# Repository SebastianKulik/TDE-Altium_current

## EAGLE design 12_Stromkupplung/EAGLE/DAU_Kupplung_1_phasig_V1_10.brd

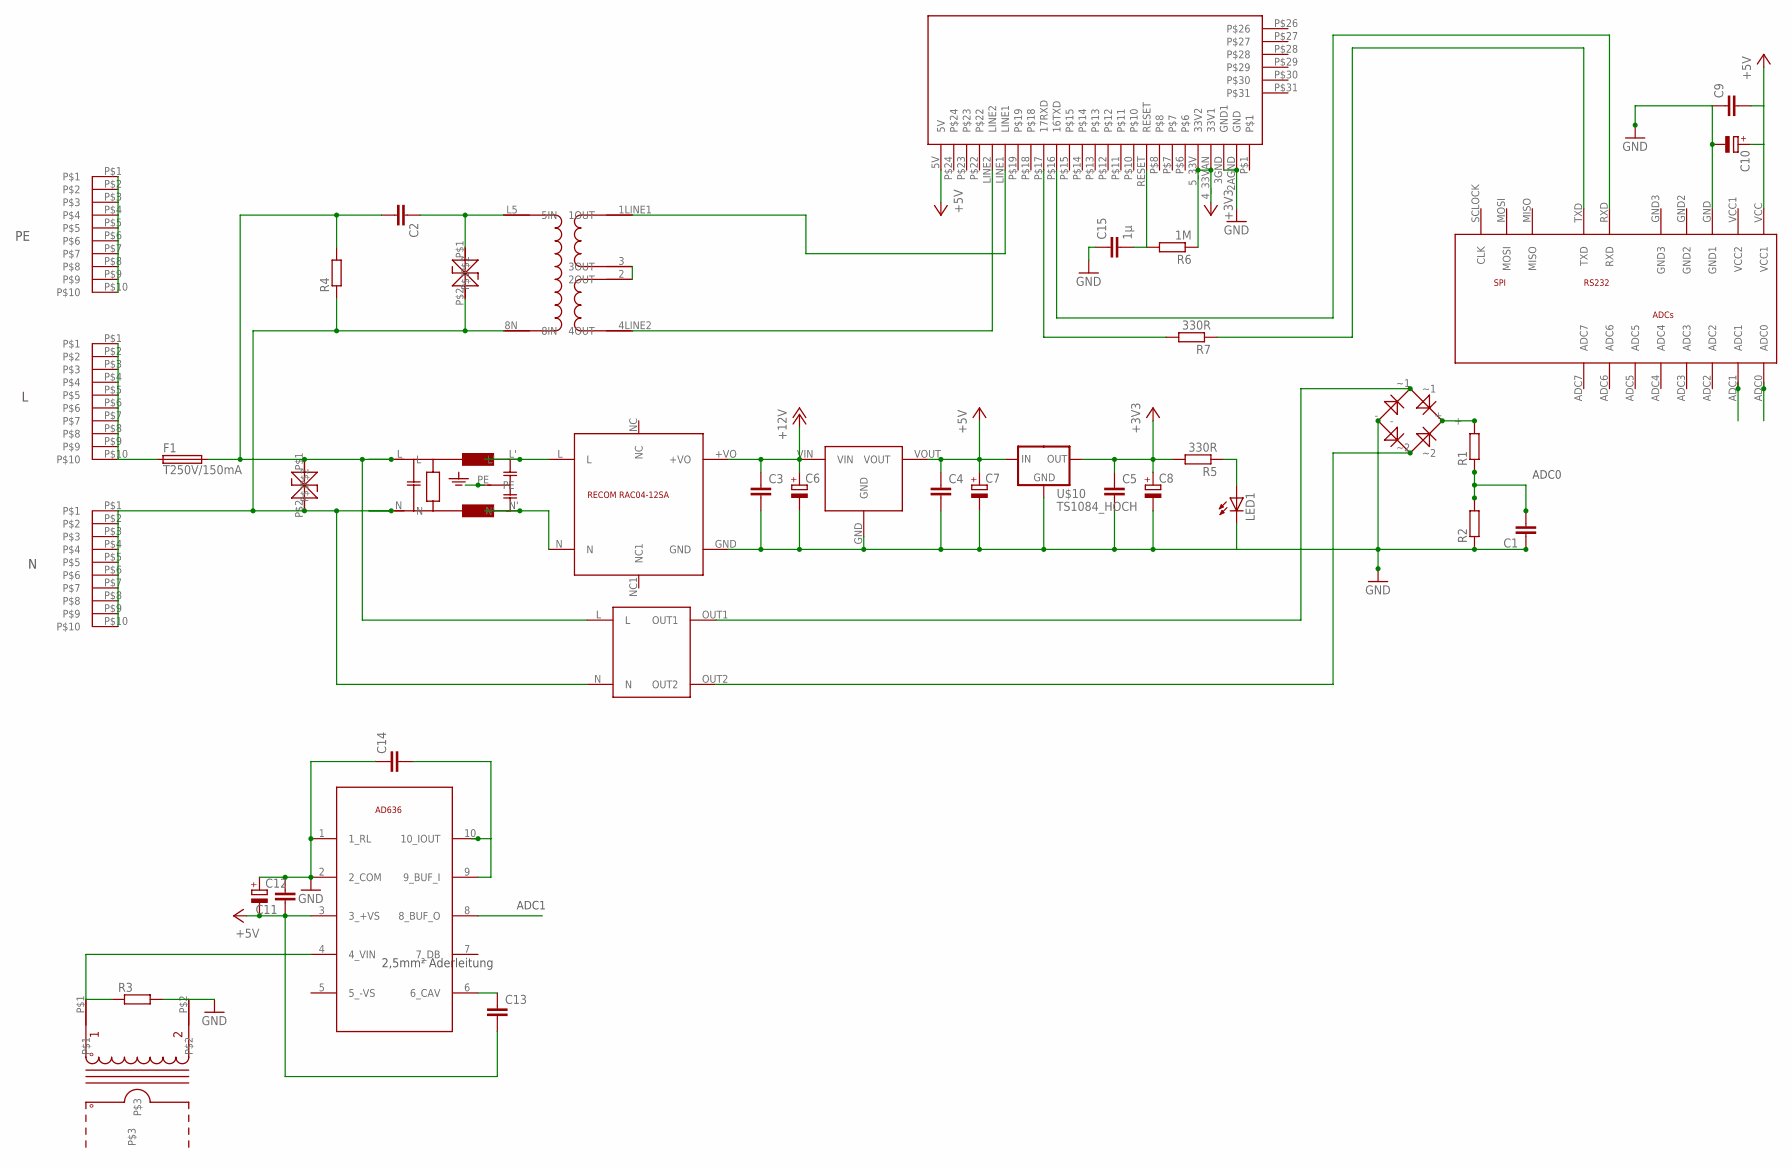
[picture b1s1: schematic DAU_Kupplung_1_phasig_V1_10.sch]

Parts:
C1: C2,5-3; C2.5-3
C2: C-EU225-087X268; C225-087X268
C3, C4, C5, C9, C11, C13, C14: C-EUC0805; C0805
C6, C7, C8: CPOL-EUE2.5-6; E2,5-6
C10, C12: CPOL-EUE2,5-6E; E2,5-6E
C15: 1µ; C0805
F1: T250V/150mA; TR5
L: PRINT_CONNECTOR; FASTON_DOUBLE
LED1: LEDSQR2X5; LED2X5
N: PRINT_CONNECTOR; FASTON_DOUBLE
PE: PRINT_CONNECTOR; FASTON_DOUBLE
R1, R2, R3, R4: R-EU_0204/7; 0204/7
R5, R7: 330R; 0204/7
R6: 1M; 0204/7
U$1: RECOM_RAC04_12SA; RAC04_12SA
U$2: SICHERHEITSTRAFO; TRAFO_0,35VA
U$3: ADUC831_MINIMUM; ADUC_MINIMUM
U$4: IT800
U$5: PLC_UEBERTRAGER_V2; PLC-UEBERTRAGER_V2
U$6: AC1010
U$7: AD636; TO100_10PIN
U$8: RECTIFIER
U$9, U$12: TSV
U$10: TS1084_HOCH
U$11: RECOM_785_05; RECOM785X
U$13: NETZFILTER_05_A; NETZFILTER

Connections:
+3V3: C5.1, C8.+, R5.2, R6.1, U$4.4_33VAN (33V1), U$4.5_33V (33V2), U$10.OUT
+5V: C4.1, C7.+, C9.2, C10.+, C11.1, C12.-, C13.2, U$3.VCC (VCC1), U$4.5V, U$7.3 (3_+VS), U$10.IN, U$11.VOUT
+12V: C3.1, C6.+, U$1.+VO, U$11.VIN
ADC0: C1.2, R1.1, R2.2, U$3.ADC0
ADC1: U$3.ADC1, U$7.8 (8_BUF_O)
GND: C1.1, C3.2, C4.2, C5.2, C6.-, C7.-, C8.-, C9.1, C10.-, C11.2, C12.+, C14.1, C15.1, LED1.K (C), R2.1, R3.2, U$1.GND, U$3.GND (GND1), U$4.2AGND (GND), U$4.3GND (GND1), U$6.P$2, U$7.1 (1_RL), U$7.2 (2_COM), U$8.-, U$10.GND, U$11.GND
unnamed: U$5.2 (2OUT), U$5.3 (3OUT)
unnamed: R7.2, U$4.P$17 (17RXD)
unnamed: U$2.OUT1, U$8.~1
unnamed: U$4.LINE1, U$5.1LINE1 (1OUT)
unnamed: F1.1, L.P$1, L.P$2, L.P$3, L.P$4, L.P$5, L.P$6, L.P$7, L.P$8, L.P$9, L.P$10
unnamed: R1.2, U$8.+
unnamed: R3.1, U$6.P$1, U$7.4 (4_VIN)
unnamed: U$2.OUT2, U$8.~2
unnamed: C2.1, U$5.L5 (5IN), U$12.P$1
unnamed: C2.2, F1.2, R4.2, U$2.L, U$9.P$1, U$13.L
unnamed: U$4.LINE2, U$5.4LINE2 (4OUT)
unnamed: R7.1, U$3.TXD
unnamed: U$3.RXD, U$4.P$16 (16TXD)
unnamed: C14.2, U$7.9 (9_BUF_I), U$7.10 (10_IOUT)
unnamed: C13.1, U$7.6 (6_CAV)
unnamed: N.P$1, N.P$2, N.P$3, N.P$4, N.P$5, N.P$6, N.P$7, N.P$8, N.P$9, N.P$10, R4.1, U$2.N, U$5.8N (8IN), U$9.P$2, U$12.P$2, U$13.N
unnamed: LED1.A, R5.1
unnamed: C15.2, R6.2, U$4.RESET
unnamed: U$1.L, U$13.L'
unnamed: U$1.N, U$13.N'
PE: PE.P$1, PE.P$2, PE.P$3, PE.P$4, PE.P$5, PE.P$6, PE.P$7, PE.P$8, PE.P$9, PE.P$10, U$13.PE

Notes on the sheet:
2,5mm² Aderleitung
ADC0
ADC1

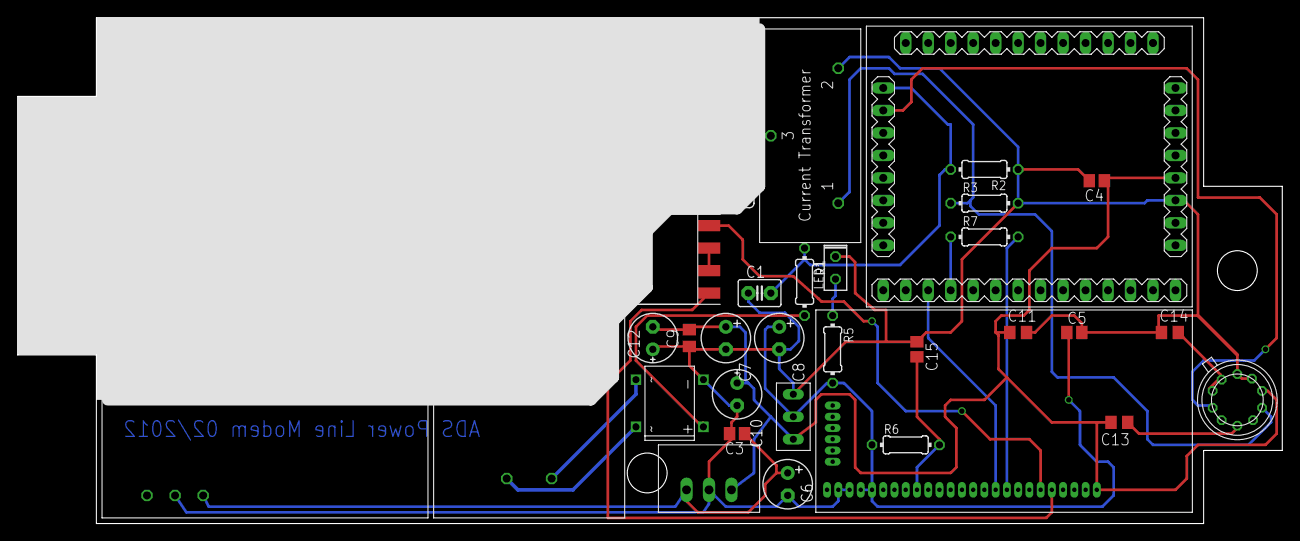
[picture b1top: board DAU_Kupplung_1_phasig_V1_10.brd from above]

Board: 2 copper layers, 142.9 x 57.1 mm, 40 parts (0 on the bottom side), 27 nets.

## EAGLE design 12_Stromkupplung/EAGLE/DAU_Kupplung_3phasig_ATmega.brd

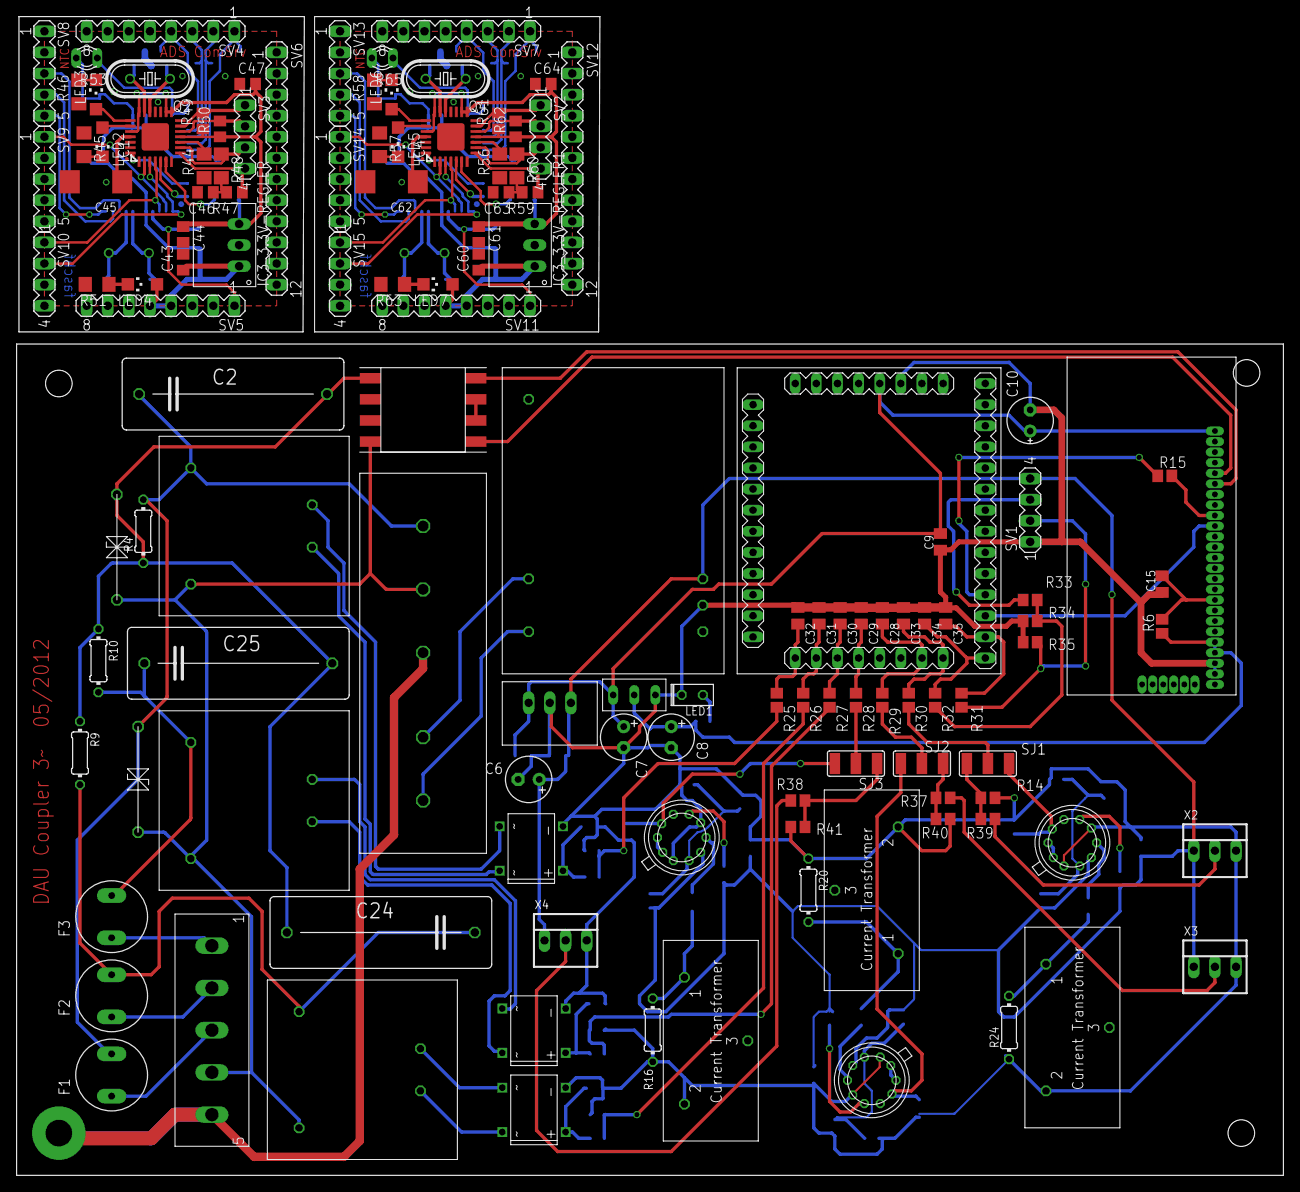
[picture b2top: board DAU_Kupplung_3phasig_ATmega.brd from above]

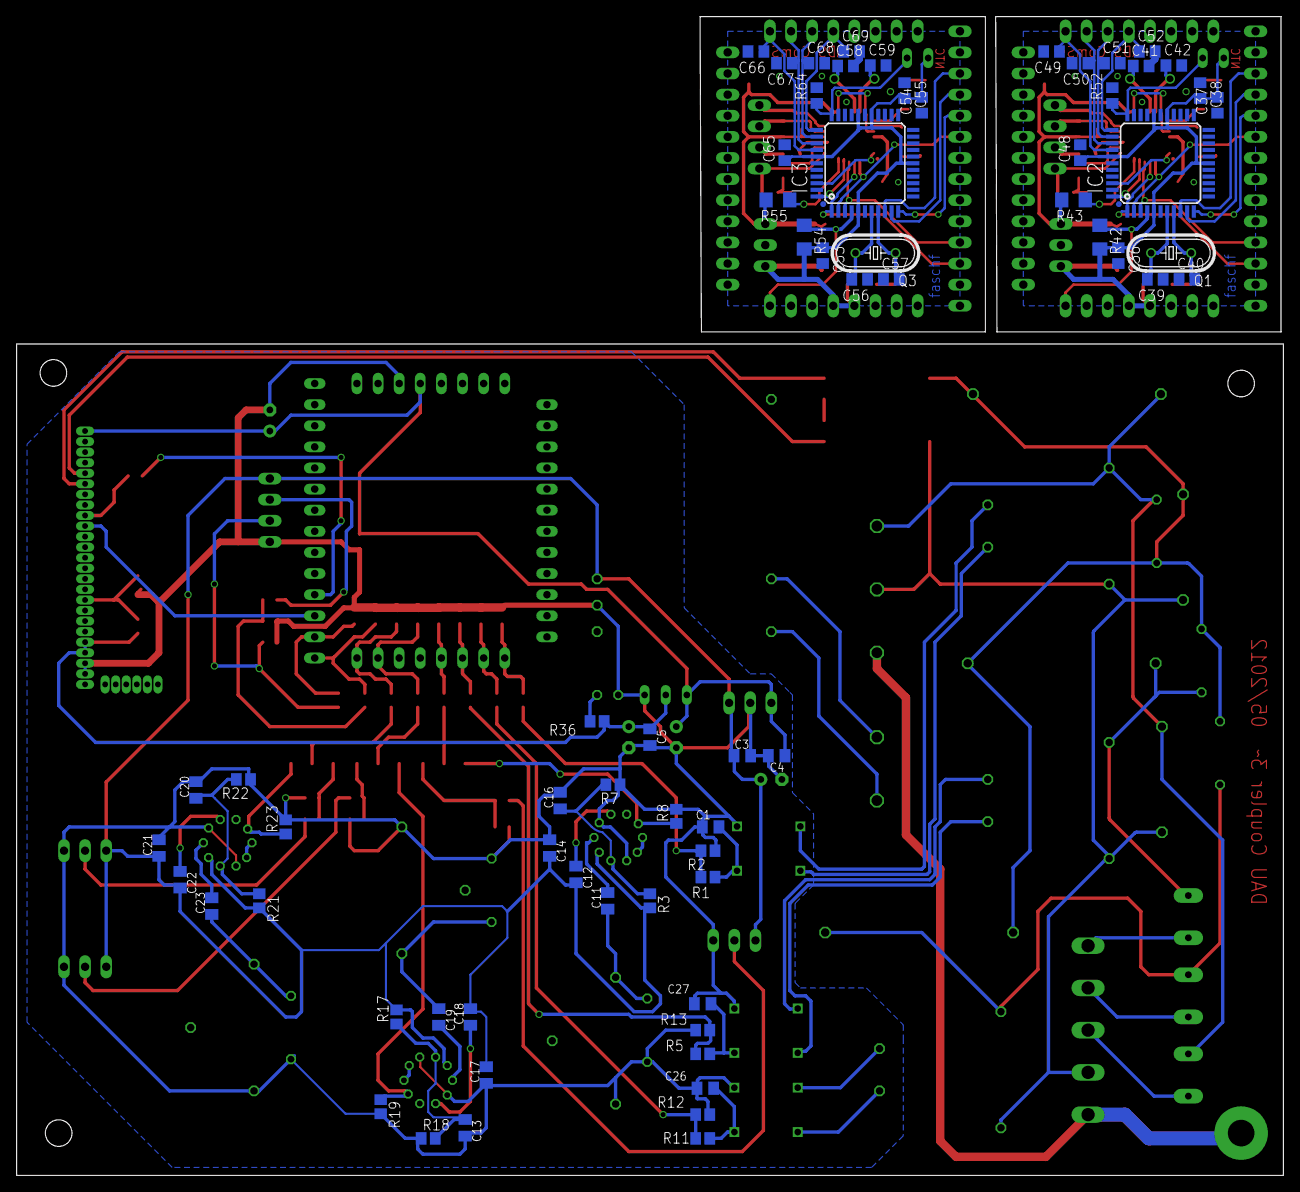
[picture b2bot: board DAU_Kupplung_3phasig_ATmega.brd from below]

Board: 2 copper layers, 152.4 x 139.4 mm, 197 parts (68 on the bottom side), 141 nets.

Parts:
AC1002_1: AC1010
C1, C11, C13, C14, C15, C16, C17, C19, C20, C21, C23, C26, C27: 1µ; C0805K
C2, C24, C25: 470n/270V; C225-087X268
C3, C4, C5, C9, C28, C29, C30, C31, C32, C33, C34, C35: 100n; C0805K
C6, C7, C8: 4,7µ; E2,5-6
C10: 4µ7; E2,5-6E
C12, C18, C22: 4µ7; C0805K
C36, C37, C38, C43, C44, C48, C53, C54, C55, C60, C61, C65: 100n; C0805
C39, C40, C41, C42, C56, C57, C58, C59: 22p; C0805
C45, C62: 10u; SMC_D
C46, C47, C49, C50, C51, C52, C63, C64, C66, C67, C68, C69: 10n; C0805
F1, F2, F3: T250mA/240V; TR5
IC1, IC4: ENC28J60QFN28_LONG_28; QFN28_LONG_ERRLES
IC2, IC3: MEGA32-A; TQFP44
IC3_3.3V-REGLER, IC3_3.3V-REGLER1: 78RECOM; RECOM_3POL
LED1: LED2X5
LED2, LED3, LED4, LED5, LED6, LED7: CHIPLED_1206
P6KE300CA: P6KE300CA; TSV
Q1, Q3: 16MHz; HC49/S
Q2, Q4: 25MHz; HC49/S
R1, R5, R11: 82k; R0805
R2, R12, R13: 33k; R0805
R3, R17, R21: 22k; R0805
R4, R9, R10: 470k; 0204/7
R6: 1M; R0805
R7, R18, R22, R52, R64: 10k; R0805
R8, R19, R23: 4k7; R0805
R14, R40, R41: 220R/33k; R0805
R15, R36: 330R; R0805
R16, R20, R24: 68R; 0204/7
R25, R26, R27, R28, R29, R30, R31, R32: 10R; R0805
R33: 680k; R0805
R34: 470k; R0805
R35: 220R; R0805
R37, R38, R39: 0/82k; R0805
R42, R43, R54, R55: 10k; R1206
R44, R56: 2k2; R1206
R45, R46, R51, R57, R58, R63: 220R; R1206
R47, R49, R50, R59, R61, R62: 51R; R0805
R48, R60: 51R; R1206
R53, R65: P640
SJ1, SJ2, SJ3: SJ_2W
SV1, SV2, SV3, SV10, SV15: MA04-1
SV4, SV5, SV7, SV11: MA08-1
SV6, SV12: MA12-1
SV8, SV9, SV13, SV14: MA05-1
TSV2: TSV
U$1: RECOM_RAC04_12SA; RAC04_12SA
U$2, U$16, U$18: SICHERHEITSTRAFO; TRAFO_0,35VA
U$3: ADUC831_MINIMUM; ADUC_MINIMUM
U$4: MODEMSTECKER; MODEM_FUSS
U$5: PLC_UEBERTRAGER_V2; PLC-UEBERTRAGER_V2
U$7, U$14: AC1010
U$8, U$17, U$19: RECTIFIER
U$10: RECOM_785_05; RECOM785X
U$11: TS1084_HOCH
U$12, U$13, U$15: AD536; TO100_10PIN
U$20: NETZFILTER_05_A; NETZFILTER
X1: CONNECTO_5_POL; CONNECTOR_5_POL
X2, X3, X4: 22-23-2031

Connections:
1_TD+: IC1.13, R49.2, SV3.1
1_TD+1: IC4.13, R61.2, SV2.1
2_TD-: IC1.12, R50.2, SV3.2
2_TD-1: IC4.12, R62.2, SV2.2
3_RD+: IC1.9, R48.1, SV3.3
3_RD+1: IC4.9, R60.1, SV2.3
6_RD-: IC1.8, R47.1, SV3.4
6_RD-1: IC4.8, R59.1, SV2.4
+3V3: C5.1, C8.+, R6.1, R36.1, U$4.P$4, U$4.P$5, U$11.OUT
+5V: C4.1, C7.+, C9.2, C10.+, U$3.VCC, U$4.P$25, U$10.VOUT, U$11.IN
+12V: C3.1, C6.+, C12.2, C14.2, C17.2, C18.2, C21.1, C22.2, R3.2, R17.2, R21.2, SV1.4, U$1.+VO, U$10.VIN, U$12.3, U$13.3, U$15.3, X2.1, X3.1, X4.1
ADC0: C32.1, R25.2, U$3.ADC0
ADC1: C31.1, R26.2, U$3.ADC1
ADC2: C30.1, R27.2, U$3.ADC2
ADC3: C29.1, R28.2, U$3.ADC3
ADC4: C28.1, R29.2, U$3.ADC4
ADC5: C33.1, R30.2, U$3.ADC5
ADC6: C49.1, IC2.37, SV4.1
ADC7: C50.1, IC2.36, SV4.2
ADC8: C51.1, IC2.35, SV4.3
ADC9: C52.1, IC2.34, SV4.4
ADC10: C66.1, IC3.37, SV7.1
ADC11: C67.1, IC3.36, SV7.2
ADC12: C68.1, IC3.35, SV7.3
ADC13: C69.1, IC3.34, SV7.4
GND: AC1002_1.P$2, C1.2, C3.2, C4.2, C5.2, C6.-, C7.-, C8.-, C9.1, C10.-, C13.2, C14.1, C15.1, C16.2, C17.1, C20.2, C21.2, C26.2, C27.2, C28.2, C29.2, C30.2, C31.2, C32.2, C33.2, C34.2, C35.2, LED1.K, R2.1, R7.1, R8.2, R12.1, R13.1, R14.1, R16.1, R18.1, R19.2, R20.1, R22.1, R23.2, R24.1, R34.1, R35.1, R40.1, R41.1, SV1.1, U$1.GND, U$3.GND, U$4.P$2, U$4.P$3, U$7.P$2, U$8.-, U$10.GND, U$11.GND, U$12.1, U$12.5, U$13.1, U$13.5, U$14.P$2, U$15.1, U$15.5, U$17.-, U$19.-, X2.3, X3.3, X4.3
GND1: C36.2, C37.1, C38.1, C39.1, C40.1, C41.2, C42.2, C43.2, C44.2, C45.-, C46.2, C47.1, C48.2, C49.2, C50.2, C51.2, C52.2, IC1.7, IC1.14, IC1.17, IC1.18, IC1.26, IC2.6, IC2.18, IC2.28, IC2.30, IC2.31, IC2.32, IC2.39, IC3_3.3V-REGLER.2, R44.1, R45.1, R46.1, R51.2, R52.2, SV5.2, SV5.3, SV5.6
GND2: C53.2, C54.1, C55.1, C56.1, C57.1, C58.2, C59.2, C60.2, C61.2, C62.-, C63.2, C64.1, C65.2, C66.2, C67.2, C68.2, C69.2, IC3.6, IC3.18, IC3.28, IC3.30, IC3.31, IC3.32, IC3.39, IC3_3.3V-REGLER1.2, IC4.7, IC4.14, IC4.17, IC4.18, IC4.26, R56.1, R57.1, R58.1, R63.2, R64.2, SV11.2, SV11.3, SV11.6
I1: R28.1, SJ3.2
I1INTERN: R8.1, SJ3.3, U$13.8
I2: R29.1, SJ2.2
I2INTERN: R19.1, SJ2.3, U$12.8
I3: R30.1, SJ1.2
I3INTERN: R23.1, SJ1.3, U$15.8
INT0: IC2.11, SV8.5
INT1: IC3.11, SV13.5
L1: C2.1, F1.2, P6KE300CA.P$1, R4.2, U$2.L, U$20.L
L2: C24.1, F2.2, R9.2, U$16.L
L3: C25.1, F3.2, R10.2, U$18.L
MISO: IC1.2, IC2.2, SV9.1
MISO1: IC3.2, IC4.2, SV14.1
MOSI: IC1.3, IC2.1, SV10.2
MOSI1: IC3.1, IC4.3, SV15.2
N: P6KE300CA.P$2, TSV2.P$2, U$2.N, U$5.8N, U$16.N, U$18.N, U$20.N, X1.P$4
unnamed: R15.2, U$4.P$17
unnamed: AC1002_1.P$1, C11.1, R16.2
unnamed: C11.2, U$13.4
unnamed: U$2.OUT1, U$8.~1
unnamed: U$4.P$20, U$5.1LINE1
unnamed: U$13.9, U$13.10
unnamed: C1.1, R1.2, U$8.+
unnamed: C35.1, R31.2, U$3.ADC7
unnamed: U$2.OUT2, U$8.~2
unnamed: C26.1, R11.2, U$17.+
unnamed: U$16.OUT1, U$17.~1
unnamed: U$16.OUT2, U$17.~2
unnamed: U$4.P$21, U$5.4LINE2
unnamed: R15.1, U$3.TXD
unnamed: U$3.RXD, U$4.P$16
unnamed: U$1.L, U$20.L'
unnamed: C16.1, R3.1, R7.2, U$13.2
unnamed: C40.2, IC2.8, Q1.1
unnamed: LED1.A, R36.2
unnamed: C15.2, R6.2, U$4.P$9
unnamed: C12.1, U$13.6
unnamed: C19.1, R20.2, U$7.P$1
unnamed: C19.2, U$12.4
unnamed: U$12.9, U$12.10
unnamed: C34.1, R32.2, U$3.ADC6
unnamed: C2.2, C24.2, C25.2, R4.1, R9.1, R10.1, TSV2.P$1, U$5.L5
unnamed: C13.1, R17.1, R18.2, U$12.2
unnamed: C39.2, IC2.7, Q1.2
unnamed: C18.1, U$12.6
unnamed: C23.1, R24.2, U$14.P$1
unnamed: C23.2, U$15.4
unnamed: U$15.9, U$15.10
unnamed: U$5.2, U$5.3
unnamed: C27.1, R5.2, U$19.+
unnamed: U$18.OUT1, U$19.~1
unnamed: U$18.OUT2, U$19.~2
unnamed: R33.2, SV1.3
unnamed: C20.1, R21.1, R22.2, U$15.2
unnamed: C41.1, IC1.19, Q2.1
unnamed: C22.1, U$15.6
unnamed: U$1.N, U$20.N'
unnamed: R37.2, R40.2, SJ2.1
unnamed: R37.1, X3.2
unnamed: R14.2, R39.2, SJ1.1
unnamed: F1.1, X1.P$3
unnamed: F2.1, X1.P$2
unnamed: F3.1, X1.P$1
unnamed: R32.1, R33.1, R34.2
unnamed: R31.1, R35.2, SV1.2
unnamed: R39.1, X2.2
unnamed: R38.2, R41.2, SJ3.1
unnamed: R38.1, X4.2
unnamed: C42.1, IC1.20, Q2.2
unnamed: C45.+, IC1.25
unnamed: IC1.28, IC2.42
unnamed: IC1.6, R43.1
unnamed: IC1.10, R44.2
unnamed: LED2.C, R45.2
unnamed: IC1.23, LED2.A
unnamed: IC1.22, LED3.A
unnamed: LED3.C, R46.2
unnamed: C46.1, R47.2, R48.2
unnamed: LED4.C, R51.1
unnamed: IC2.33, R52.1, R53.1
unnamed: C57.2, IC3.8, Q3.1
unnamed: C56.2, IC3.7, Q3.2
unnamed: C58.1, IC4.19, Q4.1
unnamed: C59.1, IC4.20, Q4.2
unnamed: C62.+, IC4.25
unnamed: IC3.42, IC4.28
unnamed: IC4.6, R55.1
unnamed: IC4.10, R56.2
unnamed: LED5.C, R57.2
unnamed: IC4.23, LED5.A
unnamed: IC4.22, LED6.A
unnamed: LED6.C, R58.2
unnamed: C63.1, R59.2, R60.2
unnamed: LED7.C, R63.1
unnamed: IC3.33, R64.1, R65.1
PE: U$20.PE, X1.P$5
RESET: IC2.4, R42.1, SV5.1
RESET1: IC3.4, R54.1, SV11.1
RXD: IC2.9, SV8.3
RXD1: IC3.9, SV13.3
SCK: IC1.4, IC2.3, SV10.1
SCK1: IC3.3, IC4.4, SV15.1
SS: IC1.5, IC2.44
SS1: IC3.44, IC4.5
TXD: IC2.10, SV8.4
TXD1: IC3.10, SV13.4
U1: R1.1, R2.2, R25.1
U2: R11.1, R12.2, R26.1
U3: R5.1, R13.2, R27.1
VCC_3V: C44.1, C47.2, IC1.11, IC1.15, IC1.16, IC1.21, IC1.24, IC3_3.3V-REGLER.3, R43.2, R49.1, R50.1
VCC_3V1: C61.1, C64.2, IC3_3.3V-REGLER1.3, IC4.11, IC4.15, IC4.16, IC4.21, IC4.24, R55.2, R61.1, R62.1
VCC_5V: C36.1, C37.2, C38.2, C43.1, C48.1, IC2.5, IC2.17, IC2.27, IC2.29, IC2.38, IC3_3.3V-REGLER.1, LED4.A, R42.2, R53.2, SV5.4, SV5.5
VCC_5V1: C53.1, C54.2, C55.2, C60.1, C65.1, IC3.5, IC3.17, IC3.27, IC3.29, IC3.38, IC3_3.3V-REGLER1.1, LED7.A, R54.2, R65.2, SV11.4, SV11.5
